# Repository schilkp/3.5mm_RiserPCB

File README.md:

# 3.5mm_Riser

(c) Philipp Schilk, 2020

# Summary
A small riser PCB that allows a 3.5mm Audio Jack to be elevated above the main PCB.

This allows up to two audio jacks to be mounted on top of another connector.

As this is intended as an input, the channels are grounded through a 10K resistor when no jack is inserted.
If this is undesired, R1 should not be populated.

## Status
Currently waiting on prototype.

*Design is **untested**!*

## Included

Footprint:

Symbol:

## Specifications

Audio Jack: PJ-313D-6A ([lcsc.com](https://lcsc.com/product-detail/Audio-Video-Connectors_Korean-Hroparts-Elec-PJ-313D-6A_C95463.html))

Mounting Screw: M3

Standard 2.54mm PinHeaders

## Overview

**RiserBoard_Symbol:**

The EESCHEEMA Symbol

**RiserBoard_Footprint:**

The PCBNEW footprint.
	
Also includes step files of riser boards, that if placed in the project folder/added to the footprint
improve the 3d Model.

**RiserBoard_PCB:**

KiCad Project for the RiserBoard PCB.
Also includes Schematic and gerbers.

**Doc:**

Renders

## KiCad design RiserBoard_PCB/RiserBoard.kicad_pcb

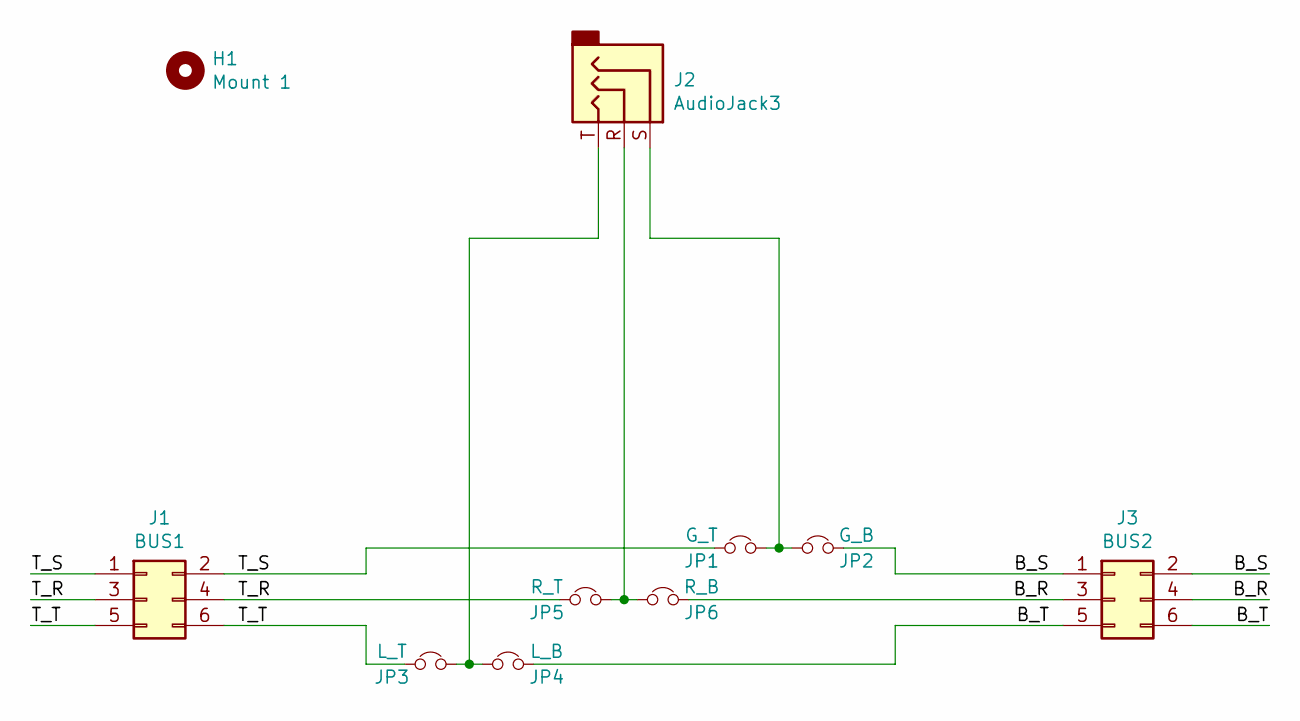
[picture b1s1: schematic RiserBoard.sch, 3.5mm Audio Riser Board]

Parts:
H1: Mount 1; MountingHole_3.2mm_M3
J1: BUS1; PinHeader_2x03_P2.54mm_Vertical
J2: AudioJack3; PJ-313D-6A
J3: BUS2; PinHeader_2x03_P2.54mm_Vertical
JP1: G_T; R_0603_1608Metric
JP2: G_B; R_0603_1608Metric
JP3: L_T; R_0603_1608Metric
JP4: L_B; R_0603_1608Metric
JP5: R_T; R_0603_1608Metric
JP6: R_B; R_0603_1608Metric

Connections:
/B_R: J3.3, J3.4, JP6.2
/B_S: J3.1, J3.2, JP2.2
/B_T: J3.5, J3.6, JP4.2
/T_R: J1.3, J1.4, JP5.1
/T_S: J1.1, J1.2, JP1.1
/T_T: J1.5, J1.6, JP3.1
unnamed: J2.R, JP5.2, JP6.1
unnamed: J2.S, JP1.2, JP2.1
unnamed: J2.T, JP3.2, JP4.1

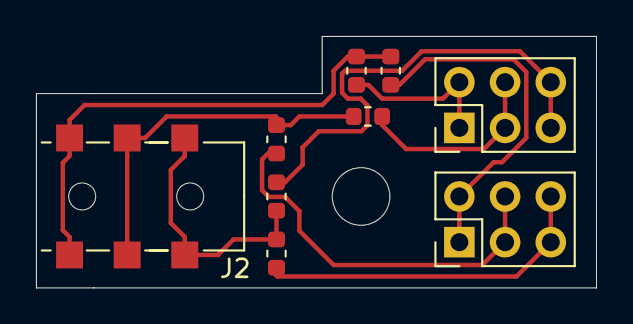
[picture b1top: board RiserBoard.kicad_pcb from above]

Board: 2 copper layers, 31.1 x 14.0 mm, 10 parts (0 on the bottom side), 9 nets.

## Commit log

2020-03-24 Added v0.0
2020-03-24 fixed small error in jack courtyard that failed DRC
2020-03-24 Fixed 3D Model Path in Footprint
2020-04-07 Fixed incorrect pad number on footprint
2020-05-24 Updated Design to v0.1
    Smaller PCB
    Only 1 sided PCB
    Different Jack Footprint
2020-05-24 Added Gerbers and new Renders
2020-05-24 Updated Page Info
2020-05-24 Associated Footprint with Symbol
2020-05-24 Made Naming of Pins consistent
2020-05-24 Rearranged Support Screw to fit pinheader under boards
2021-05-24 Added .gitattributes
